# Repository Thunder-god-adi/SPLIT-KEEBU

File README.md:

This my 42 key wireless split keyboard! It follows the corne layout I believe with a 3x6+3 layout. This is my 2nd ever PCB project, so it was very fun! It will use 42 choc switches and hotswap sockets, and is powered by a supermini nrf52840 (nice nano clone).

BOM Request for GRANT:
| Component | Quantity | Price (USD) | Source |
| --------- | -------- | ----------- | ------ |
|Supermini NRF52840| 2 | $17 | https://robu.in/product/promicro-nrf52840-development-board/
| TTC Low Profile Red Switch | 50 | $19  |https://stackskb.com/store/ttc-low-profile-red-switch-linear/?srsltid=AfmBOooBeH32TS3VNxR8EH8PzuXnoTgbSWqNrvZmlJd9rcLfo7w-K6O9nhE |
| PCB | 5 for each side | $32 | JLCPCB |
| Hotswap Sockets | 42 | $7 | https://neomacro.in/products/kailh-mx-hotswap-socket?variant=49467139227926&country=IN&currency=INR&utm_medium=product_sync&utm_source=google&utm_content=sag_organic&utm_campaign=sag_organic&srsltid=AfmBOopws6OxvTnA0HYkLtu7-fKtBb5ydNaW2wSGCo4RdlMSqB_DNmhb0o8
| Keycaps | 42 | $20 | https://neomacro.in/products/chocfox-cfx-choc-blank-keycaps?variant=48049351557398

**JLC**

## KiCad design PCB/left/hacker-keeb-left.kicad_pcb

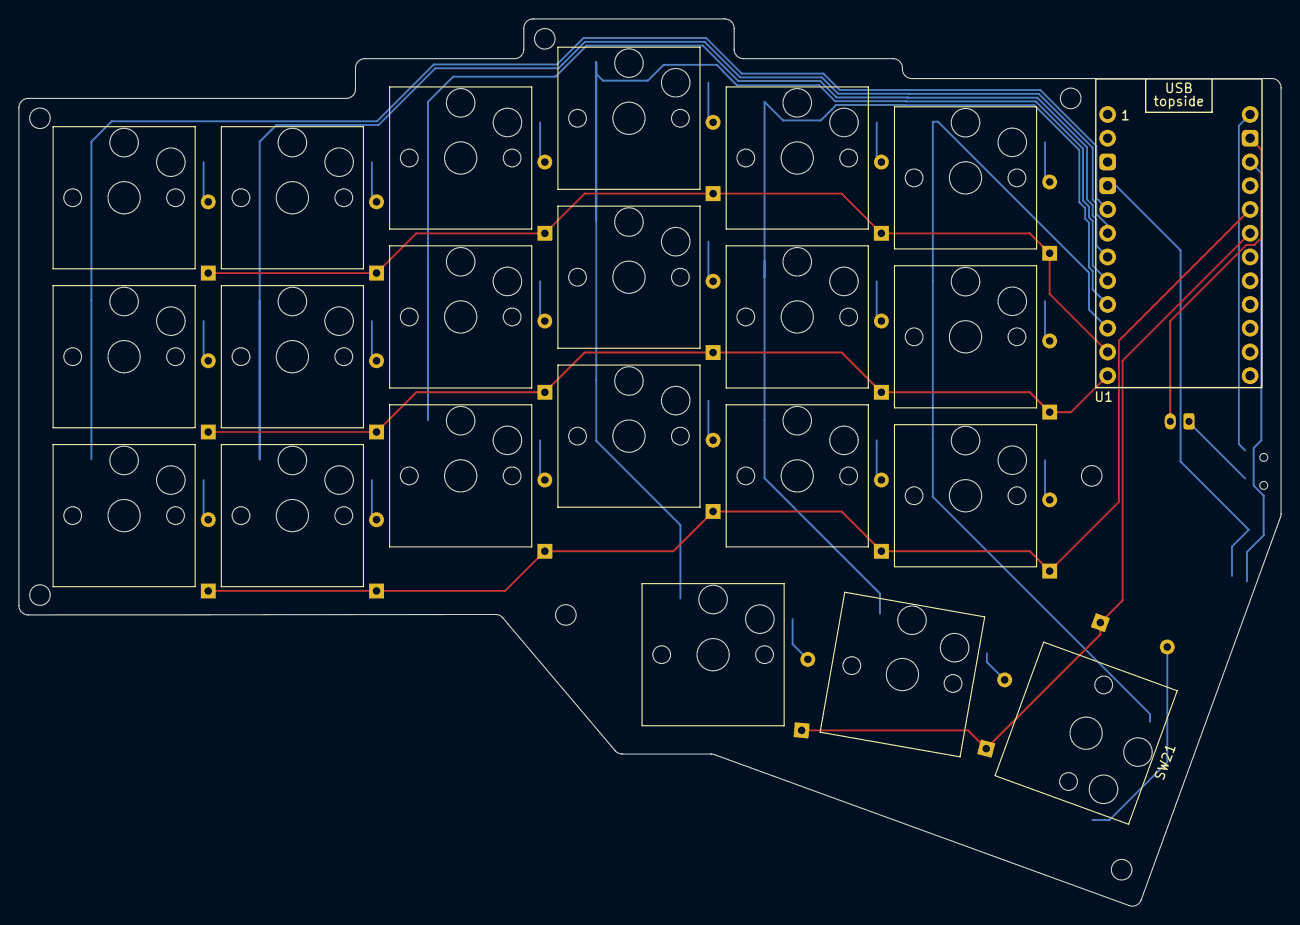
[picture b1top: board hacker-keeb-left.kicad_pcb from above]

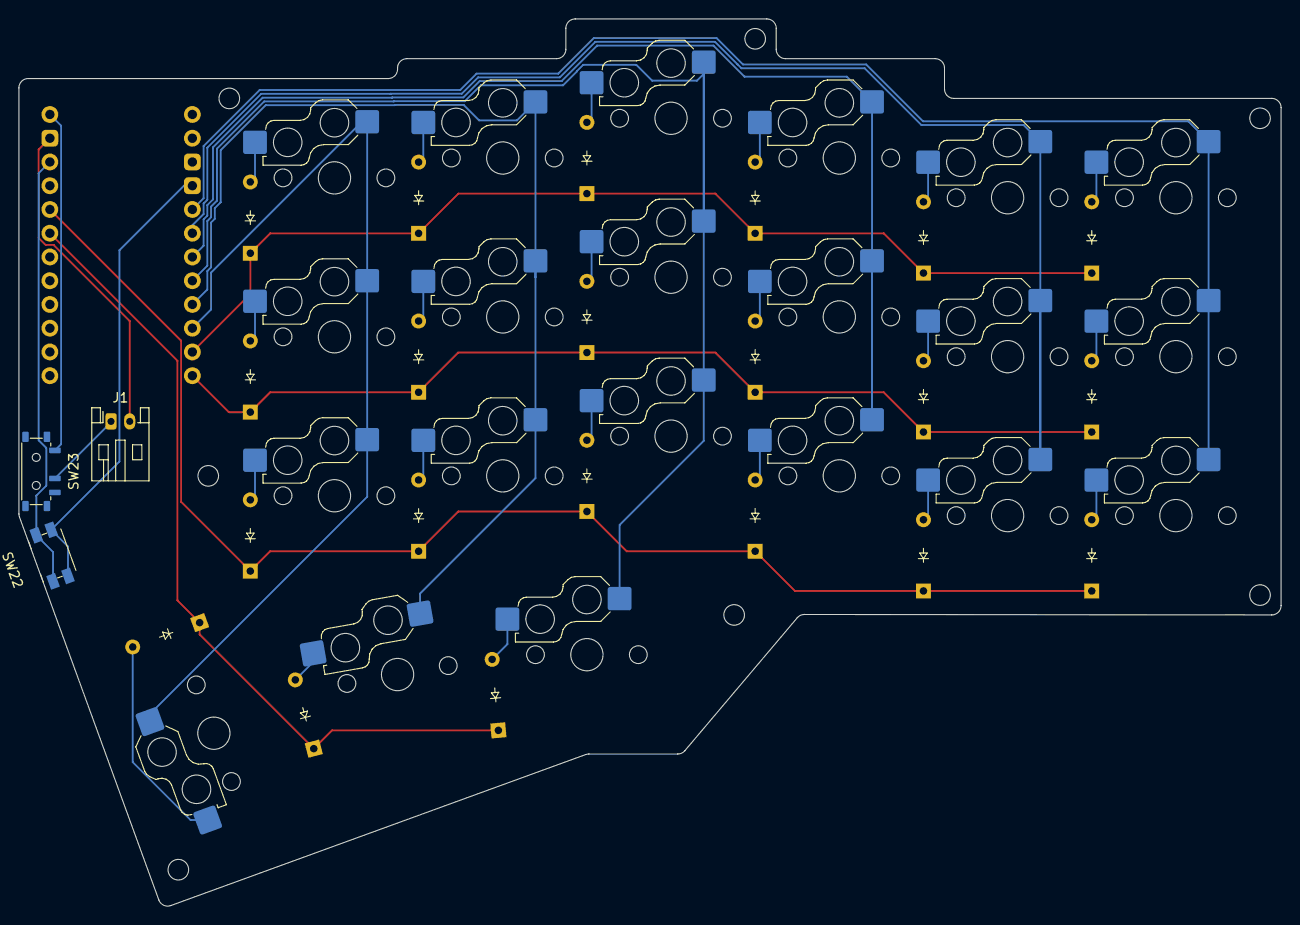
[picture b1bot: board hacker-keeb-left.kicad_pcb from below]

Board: 2 copper layers, 135.0 x 94.9 mm, 46 parts (24 on the bottom side), 36 nets.

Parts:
D1, D2, D3, D4, D5, D6, D7, D8, D9, D10, D11, D12, D13, D14, D15, D16, D17, D18, D19, D20, D21: 1N4148; Diode_DO-35
J1: Conn_01x02; JST_PH_S2B-PH-K_1x02_P2.00mm_Horizontal
SW1, SW2, SW3, SW4, SW5, SW6, SW7, SW8, SW9, SW10, SW11, SW12, SW13, SW14, SW15, SW16, SW17, SW18, SW19, SW20: Keyswitch; Hotswap_Choc_V1_1.00u
SW21: Keyswitch; Hotswap_Choc_V1_1.50u
SW22: SW_Push; Panasonic_EVQPUJ_EVQPUA
SW23: SW_SPST; Switch_MSK12C02
U1: SuperMini nRF52840; SuperMini_nRF52840_H_USBup

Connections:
Bat+: SW23.1 (A), U1.13 (BAT+)
Column 1: SW1.1, SW7.1, SW13.1, U1.5 (P0.17)
Column 2: SW2.1, SW8.1, SW14.1, U1.6 (P0.20)
Column 3: SW3.1, SW9.1, SW15.1, U1.7 (P0.22)
Column 4: SW4.1, SW10.1, SW16.1, SW19.1, U1.8 (P0.24)
Column 5: SW5.1, SW11.1, SW17.1, SW20.1, U1.9 (P1.00)
Column 6: SW6.1, SW12.1, SW18.1, SW21.1, U1.10 (P0.11)
GND(Battery): J1.2, U1.14 (GND)
GND(Reset): SW22.2, U1.4 (GND)
unnamed: D1.2 (A), SW1.2
unnamed: D2.2 (A), SW2.2
unnamed: D3.2 (A), SW3.2
unnamed: D4.2 (A), SW4.2
unnamed: D5.2 (A), SW5.2
unnamed: D6.2 (A), SW6.2
unnamed: D7.2 (A), SW7.2
unnamed: D8.2 (A), SW8.2
unnamed: D9.2 (A), SW9.2
unnamed: D10.2 (A), SW10.2
unnamed: D11.2 (A), SW11.2
unnamed: D12.2 (A), SW12.2
unnamed: D13.2 (A), SW13.2
unnamed: D14.2 (A), SW14.2
unnamed: D15.2 (A), SW15.2
unnamed: D16.2 (A), SW16.2
unnamed: D17.2 (A), SW17.2
unnamed: D18.2 (A), SW18.2
unnamed: D19.2 (A), SW19.2
unnamed: D20.2 (A), SW20.2
unnamed: D21.2 (A), SW21.2
unnamed: J1.1, SW23.2 (B)
Reset: SW22.1, U1.15 (RST)
Row 1: D1.1 (K), D2.1 (K), D3.1 (K), D4.1 (K), D5.1 (K), D6.1 (K), U1.11 (P1.04-LF)
Row 2: D7.1 (K), D8.1 (K), D9.1 (K), D10.1 (K), D11.1 (K), D12.1 (K), U1.12 (P1.06-LF)
Row 3: D13.1 (K), D14.1 (K), D15.1 (K), D16.1 (K), D17.1 (K), D18.1 (K), U1.17 (P0.31-LF)
Row 4: D19.1 (K), D20.1 (K), D21.1 (K), U1.18 (P0.29-LF)
